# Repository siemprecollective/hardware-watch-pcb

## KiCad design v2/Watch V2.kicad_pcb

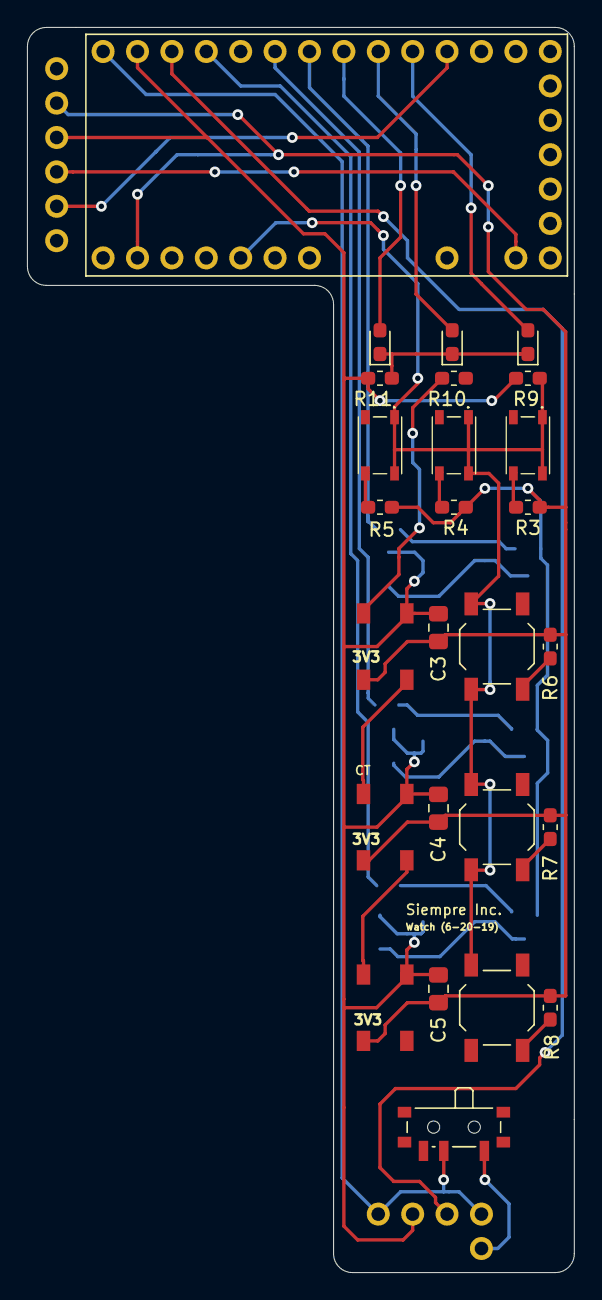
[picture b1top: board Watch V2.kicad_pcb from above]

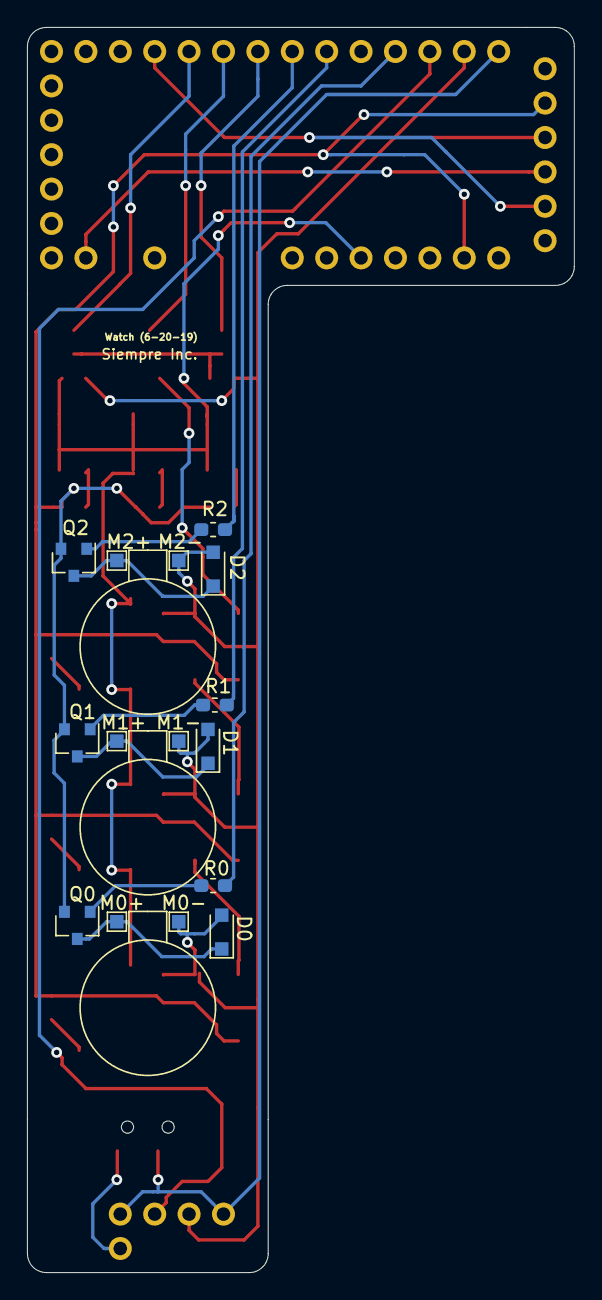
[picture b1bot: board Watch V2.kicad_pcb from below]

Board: 2 copper layers, 40.4 x 91.9 mm, 43 parts (15 on the bottom side), 27 nets.

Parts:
 : ItsyBitsyBackpack-Mount
 #2: ItsyBitsy
 #3: PinHeader_1x06_P2.54mm_Vertical
C3, C4, C5: 1 uF; C_0805_2012Metric_Pad1.15x1.40mm_HandSolder
D0, D1, D2: D; D_SOD-323_HandSoldering
D3, D4, D5: WS2812B; LED_WS2812B_PLCC4_5.0x5.0mm_P3.2mm
D-G1: LED; LED_0603_1608Metric_Pad1.05x0.95mm_HandSolder
D-R1: LED; LED_0603_1608Metric_Pad1.05x0.95mm_HandSolder
D-Y1: LED; LED_0603_1608Metric_Pad1.05x0.95mm_HandSolder
M0+: M0+; TestPoint_Pad_1.0x1.0mm
M0-: M0-; TestPoint_Pad_1.0x1.0mm
M1+: M1+; TestPoint_Pad_1.0x1.0mm
M1-: M1-; TestPoint_Pad_1.0x1.0mm
M2+: M2+; TestPoint_Pad_1.0x1.0mm
M2-: M2-; TestPoint_Pad_1.0x1.0mm
Q0, Q1, Q2: Q_PNP_BEC; SOT-23
R0, R1, R2: 270; R_0603_1608Metric_Pad1.05x0.95mm_HandSolder
R3: 33k; R_0603_1608Metric_Pad1.05x0.95mm_HandSolder
R4: 16k; R_0603_1608Metric_Pad1.05x0.95mm_HandSolder
R5: 4.3k; R_0603_1608Metric_Pad1.05x0.95mm_HandSolder
R6: 62k; R_0603_1608Metric_Pad1.05x0.95mm_HandSolder
R7: 120k; R_0603_1608Metric_Pad1.05x0.95mm_HandSolder
R8: 210k; R_0603_1608Metric_Pad1.05x0.95mm_HandSolder
R9: 43k; R_0603_1608Metric_Pad1.05x0.95mm_HandSolder
R10: 470; R_0603_1608Metric_Pad1.05x0.95mm_HandSolder
R11: 510; R_0603_1608Metric_Pad1.05x0.95mm_HandSolder
SW1: SW_DIP_x01; SW_SPDT_PCM12
SW-G1: SW_Push; SKRPADE010
SW-P1, SW-P2, SW-P3: SW_Push; SW_SPST_TL3342
SW-R1: SW_Push; SKRPADE010
SW-Y1: SW_Push; SKRPADE010

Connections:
+3V3: #2.32, #3.2, C3.1, C4.1, C5.1, D3.1, D4.1, D5.1, Q0.2, Q1.2, Q2.2, R3.2, R4.2, R5.2, R6.2, R7.2, R8.2
ANALOG0: #2.29, R9.1, SW-G1.1, SW-P1.1, SW-P2.1, SW-P3.1, SW-R1.1, SW-Y1.1
D0: #2.5, D-R1.2
D1: #2.7, D-Y1.2
D2: #2.9, D-G1.2
GND: .2, #2.2, #3.3, C3.2, C4.2, C5.2, D0.2, D1.2, D2.2, D3.3, D4.3, D5.3, M0-.2, M1-.4, M2-.6, R9.2, R11.2
M0+: D0.1, M0+.1, Q0.3
M1+: D1.1, M1+.3, Q1.3
M2+: D2.1, M2+.5, Q2.3
unnamed: D3.2, D4.4
unnamed: D3.4, R10.2
unnamed: D4.2, D5.4
unnamed: D-G1.1, D-R1.1, D-Y1.1, R11.1
unnamed: Q0.1, R0.2
unnamed: Q1.1, R1.2
unnamed: Q2.1, R2.2
unnamed: R3.1, SW-R1.2
unnamed: R4.1, SW-Y1.2
unnamed: R5.1, SW-G1.2
unnamed: R6.1, SW-P1.2
unnamed: R7.1, SW-P2.2
unnamed: R8.1, SW-P3.2
PWM0: #2.13, R0.1
PWM1: #2.11, R1.1
PWM2: #2.10, R2.1
VBAT: .1, .4, #2.1, SW1.2
VBAT-IN: .5, SW1.1

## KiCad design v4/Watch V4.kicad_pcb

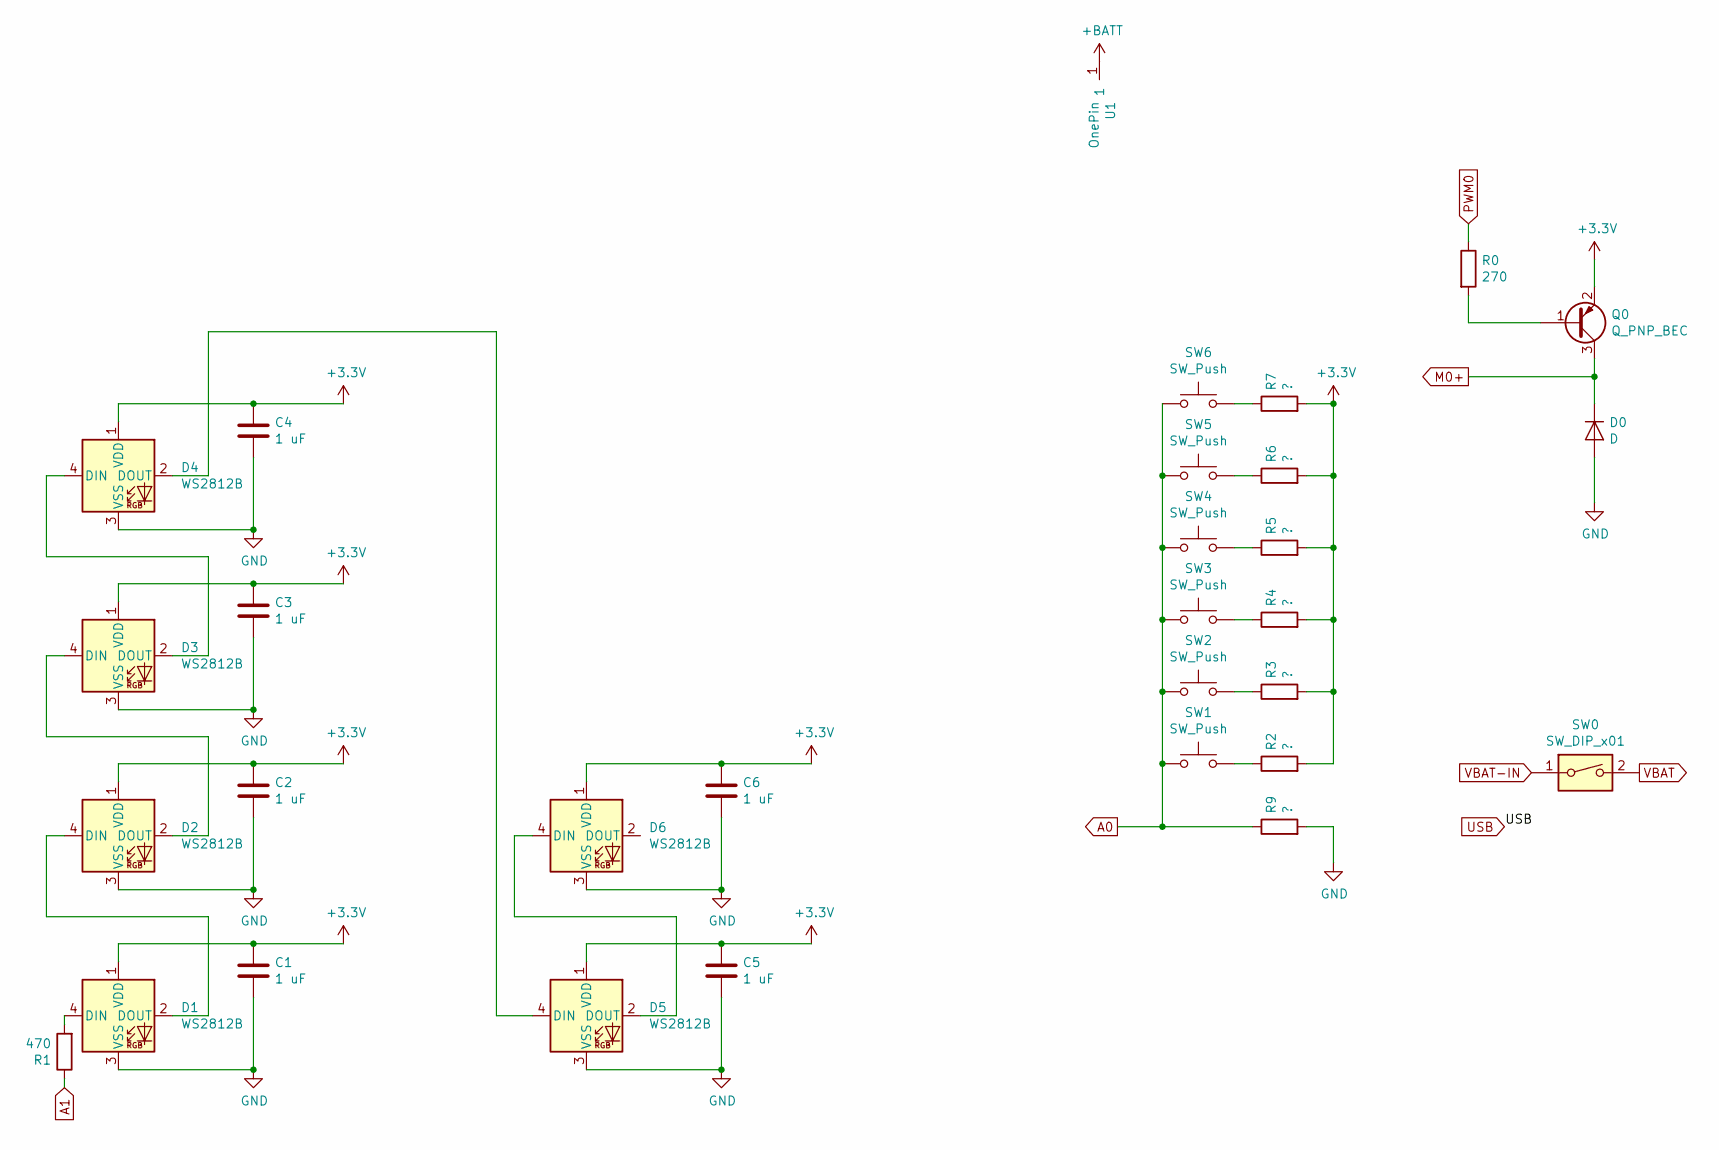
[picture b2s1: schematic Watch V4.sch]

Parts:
C1, C2, C3, C4, C5, C6: 1 uF; C_0805_2012Metric_Pad1.15x1.40mm_HandSolder; MPN VJ0805A102KXAAC
D0: D; D_SOD-323_HandSoldering; MPN 1N4148WS-7-F
D1, D2, D3, D4, D5, D6: WS2812B; LED_WS2812B_PLCC4_5.0x5.0mm_P3.2mm; MPN 1830-1106-1-ND
Q0: Q_PNP_BEC; SOT-23_Handsoldering; MPN 1N4148WS-7-F
R0: 270; R_0603_1608Metric_Pad1.05x0.95mm_HandSolder; MPN RC0603FR-07270RL
R1: 470; R_0603_1608Metric_Pad1.05x0.95mm_HandSolder; MPN RC0603FR-07470RL
R2: ?; R_0603_1608Metric_Pad1.05x0.95mm_HandSolder; MPN RC0603FR-07210KL
R3: ?; R_0603_1608Metric_Pad1.05x0.95mm_HandSolder; MPN RC0603FR-07120KL
R4: ?; R_0603_1608Metric_Pad1.05x0.95mm_HandSolder; MPN RC0603FR-0762KL
R5: ?; R_0603_1608Metric_Pad1.05x0.95mm_HandSolder; MPN RC0603FR-074K3L
R6, R7: ?; R_0603_1608Metric_Pad1.05x0.95mm_HandSolder; MPN RC0603FR-0716KL
R9: ?; R_0603_1608Metric_Pad1.05x0.95mm_HandSolder; MPN RC0603FR-0743KL
SW0: SW_DIP_x01; JS202011SCQN; MPN PCM12SMTR
SW1, SW2, SW3: SW_Push; SKRPADE010; MPN TL3342F160QG
SW4, SW5, SW6: SW_Push; SKRPADE010; MPN SKRPADE010
U1: OnePin; One Pin

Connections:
+3V3: C1.1, C2.1, C3.1, C4.1, C5.1, C6.1, D1.1 (VDD), D2.1 (VDD), D3.1 (VDD), D4.1 (VDD), D5.1 (VDD), D6.1 (VDD), Q0.2 (E), R2.2, R3.2, R4.2, R5.2, R6.2, R7.2; also elsewhere on the board
+BATT: U1.1; also elsewhere on the board
A0: R9.1, SW1.1, SW2.1, SW3.1, SW4.1, SW5.1, SW6.1; also elsewhere on the board
A1: R1.1; also elsewhere on the board
GND: C1.2, C2.2, C3.2, C4.2, C5.2, C6.2, D0.2 (A), D1.3 (VSS), D2.3 (VSS), D3.3 (VSS), D4.3 (VSS), D5.3 (VSS), D6.3 (VSS), R9.2; also elsewhere on the board
M0+: D0.1 (K), Q0.3 (C); also elsewhere on the board
unnamed: D1.2 (DOUT), D2.4 (DIN)
unnamed: D1.4 (DIN), R1.2
unnamed: D2.2 (DOUT), D3.4 (DIN)
unnamed: D3.2 (DOUT), D4.4 (DIN)
unnamed: D4.2 (DOUT), D5.4 (DIN)
unnamed: D5.2 (DOUT), D6.4 (DIN)
unnamed: Q0.1 (B), R0.2
unnamed: R2.1, SW1.2
unnamed: R3.1, SW2.2
unnamed: R4.1, SW3.2
unnamed: R5.1, SW4.2
unnamed: R6.1, SW5.2
unnamed: R7.1, SW6.2
PWM0: R0.1; also elsewhere on the board
VBAT: SW0.2; also elsewhere on the board
VBAT-IN: SW0.1; also elsewhere on the board

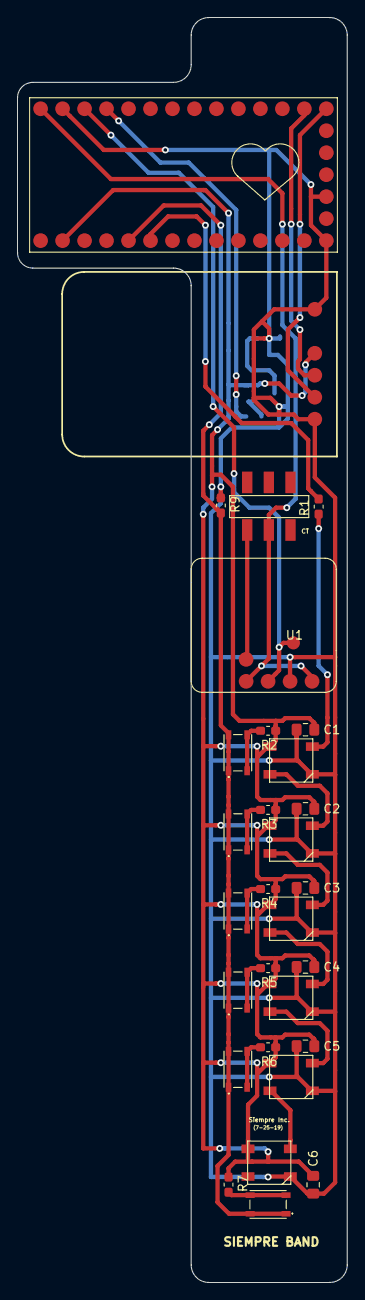
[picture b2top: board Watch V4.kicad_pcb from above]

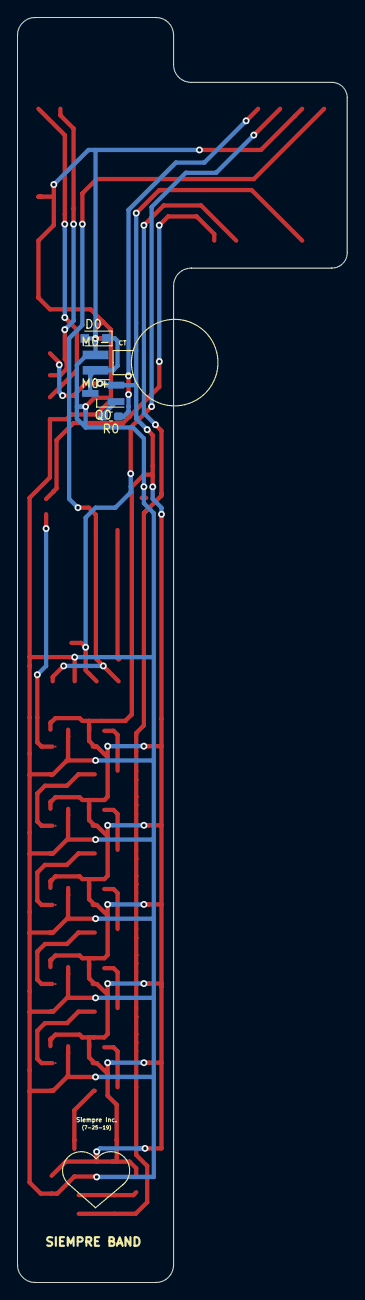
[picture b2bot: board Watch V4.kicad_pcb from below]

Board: 2 copper layers, 38.1 x 146.2 mm, 36 parts (5 on the bottom side), 22 nets.

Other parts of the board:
 : Bluefruit-LE-UART-Friend
 #2: ItsyBitsy
 #3: ItsyBitsyBackpack-Mount
M0+: M0+; TestPoint_Pad_1.0x1.0mm
M0-: M0-; TestPoint_Pad_1.0x1.0mm

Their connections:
+3V3: .VIN, #2.3V; also elsewhere on the board
+BATT: #2.USB, #3.3; also elsewhere on the board
A0: #2.A0; also elsewhere on the board
A1: #2.A1; also elsewhere on the board
GND: .CTS, .GND, #2.G, #3.2, M0-.2; also elsewhere on the board
M0+: M0+.1; also elsewhere on the board
PWM0: #2.13; also elsewhere on the board
VBAT: #2.VBAT, #3.1, #3.4; also elsewhere on the board
VBAT-IN: #3.5; also elsewhere on the board

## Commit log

2020-08-22 First release to public domain
